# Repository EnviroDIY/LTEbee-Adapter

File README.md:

EnviroDIY LTE Bee Adapter
==============
The EnviroDIY LTE Bee Adapter shield is an interface board designed to enhance the functioning and stability of the [Digi XBee3 Cellular LTE-M/NB-IoT](https://www.digi.com/products/embedded-systems/cellular-modems/xbee3-cellular-lte-m-nb-iot) radio modules with the [EnviroDIY Mayfly Logger versions 0.5b](https://github.com/EnviroDIY/EnviroDIY_Mayfly_Logger) or earlier.

The [EnviroDIY LTE Bee Adapter shield can be purchased at Amazon.com](https://www.amazon.com/Stroud-Water-Research-Center-EnviroDIY/dp/B07TRHHMDJ).

The two main benefits of the LTE adapter board are:
- additional features for power supply, stability and switching
- status LED lights 

|  
|  
|  
|  |

The power benefits are provided via a direct JST connector to the battery, similar to Sodaq GPRSbee modules, and a capacitor chain. Power is thus much smoother, and the XBee module should not brown out and stop communicating.  Use a JST jumper wire to connect the LTEbee adapter board to the spare LIPO jack on the Mayfly board.

There are 3 colored LEDs on the LTEbee adapter.
- ON (white) light comes on anytime the LTEbee is awake.
- ASSOC (blue) light is connected to the ASSOC pin of the bee module, and will blink different patterns to show the connection status to the network.
- RSSI (orange) light is the received signal strength indicator.  It will turn on when connecting with the network vary in brightness depending on signal strength. 

DO NOT UNPLUG the LTEbee Adapter board while any of the lights are on, as this might permanently lockup your Digi radio module. Powering down the Mayfly should put set the LTEbee Adapter to put the radio into sleep mode, and this might take a minute or so after turning the Mayfly off. 

If using a Mayfly v0.5b, you'll want to make sure that the SJ13 solder jumper is in the configuration where pin 1 of the 
Mayfly bee header is powered by the 3.3Vcc and not directly to the LiPo (this is the default jumper setting).  This way, the Mayfly's bee socket only gets power whenever the Mayfly is turned on, and the LTEbee module doesn't wake up when the Mayfly is off (which is what it does if the LiPo is directly connected to bee pin 1 via SJ13).  You can then control the LTEbee module's sleep behavior with the module's pin 9 sleep pin (using Mayfly D23).

We also have access to the LTE module's reset pin now. If using the Mayfly and the ModularSensors library, the user can set the reset pin to Mayfly pin 20 in the constructor for the modem in the code sketch. Currently the only time that feature is used, though, is in transparent mode if it doesn’t reply after 4 attempts to enter command mode.  In watching the debugging logs, we haven’t seen it use that reset yet. 

The LTEbee Adapter shield also has two a solder jumper's on the back, giving the user configuration options.

The LTEbee Adapter's **SJ1 solder jumper** allows the user to select how to power the load switch for the Vcc pin of the module.  
- The default setting is that the LTE module is always powered when the Mayfly bee socket Vcc pin (pin 1) is on (as mentioned above).
- If you switch the jumper to the other position (Mayfly A5), it allows you to turn on and off the power to the LTEbee by using pin 15 of the Mayfly bee socket, which goes to the Mayfly's SJ7 solder jumper:  
  - [Mayfly SJ7](https://github.com/EnviroDIY/EnviroDIY_Mayfly_Logger#solder-jumper-connections) was originally designed to allow you to connect Mayfly pin A5 to either the RingIndicator pin (Bee 20) or the Assoc pin (Bee 15). The default is not connected to either (all pads open).
  - If you solder the Mayfly SJ7 jumper between the A5 and ASSOC pads, you are then connecting A5 to the Mayfly bee socket pin 15, which goes to SJ1 on the LTEbee_adapter, allowing you to turn on or off the LTEbee by setting A5 high or low.  We aren't sure anyone would want to do that -- since Digi recommends leaving power to the LTEbee on all the time and then command it to sleep using the sleep pin (Bee 9), rather than yanking power away from it whenever you want to turn it off -- but we added this feature to give us flexiblity in the future.

The LTEbee Adapter's **SJ2 solder jumper** is for selecting which pin on the Bee modules gets connected to Mayfly D19 (Mayfly bee header pin 12).  The default setting is for the LTEBee module's pin 13 to be connected to Mayfly D19, which is how this adapter should always be used with a Digi LTEbee, but changing SJ2 to the other setting will connect pin 12 of the bee module to D19.  This was done in case other manufacturers use the same pinout as the GPRSbee boards, which are different than the Digi LTEbee.

## License
Hardware designs shared are released, unless otherwise indicated, under the [CERN Open Hardware License 1.2](https://www.ohwr.org/projects/cernohl/wiki) (CERN_OHL).

Documentation is licensed as [Creative Commons Attribution-ShareAlike 4.0](https://creativecommons.org/licenses/by-sa/4.0/) (CC-BY-SA) copyright.

## Credits
[EnviroDIY](http://envirodiy.org/)™ is presented by the Stroud Water Research Center, with contributions from a community of enthusiasts sharing do-it-yourself ideas for environmental science and monitoring.

[Shannon Hicks](https://github.com/s-hicks2) is the primary developer of this hardware, with input from many other contributors.

This project has benefited from the support from the following funders:

* William Penn Foundation
* US Environmental Protection Agency (EPA)
* National Science Foundation, awards [EAR-0724971](http://www.nsf.gov/awardsearch/showAward?AWD_ID=0724971), [EAR-1331856](http://www.nsf.gov/awardsearch/showAward?AWD_ID=1331856), [ACI-1339834](http://www.nsf.gov/awardsearch/showAward?AWD_ID=1339834)
* Stroud Water Research Center endowment

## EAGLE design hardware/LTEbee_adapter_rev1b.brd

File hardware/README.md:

Hardware Design Files
==============

Here we provide hardware design files including [EAGLE PCB electronic design files](https://github.com/EnviroDIY/EnviroDIY_Mayfly_Logger/blob/master/hardware/Mayfly_v0p5b), for use with the EAGLE electronic design automation (EDA) software (a [free maker edition](https://www.autodesk.com/products/eagle/compare) is available).

See our Documentation pages for additional details.

For questions, use our Q&A forum at https://envirodiy.org.

## Hardware Design Credits

This hardware was developed by [Shannon Hicks](https://github.com/s-hicks2).

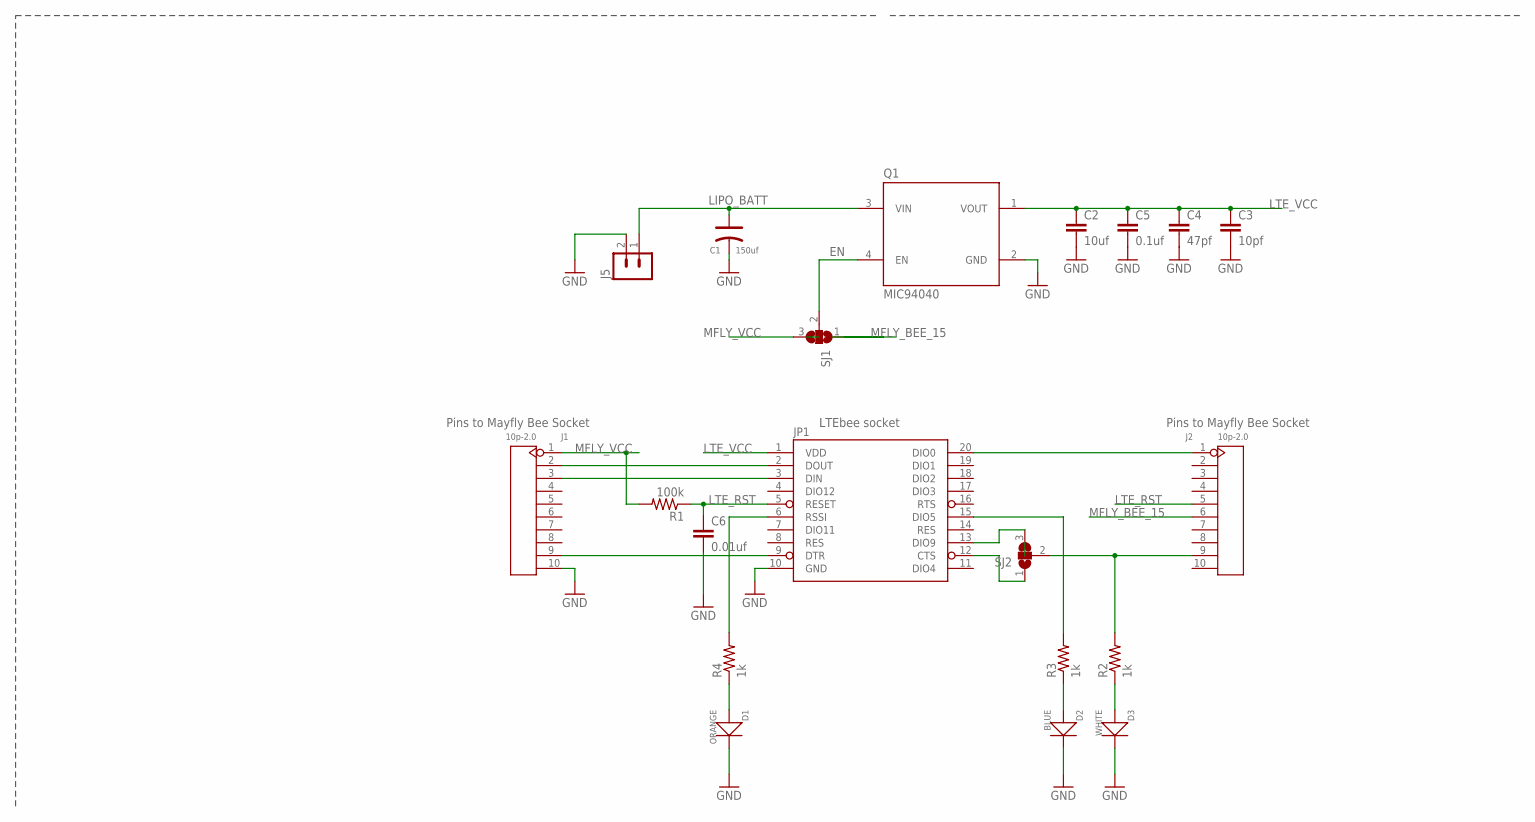
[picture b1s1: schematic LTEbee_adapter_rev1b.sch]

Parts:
C1: 150uf; AVX-B
C2: 10uf; 0402-CAP
C3: 10pf; 0402-CAP
C4: 47pf; 0402-CAP
C5: 0.1uf; 0402-CAP
C6: 0.01uf; 0402-CAP
D1: ORANGE; SOD-523
D2: BLUE; SOD-523
D3: WHITE; SOD-523
J1, J2: 10p-2.0; H10-2.0
J5: B2B-PH-K-S
JP1: XBEE-1B1; XBEE-1
Q1: MIC94040; MLF4
R1: 100k; 0603-RES
R2, R3, R4: 1k; 0603-RES
SJ1, SJ2: SJ2W; SJ_2

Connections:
EN: Q1.4 (EN), SJ1.2
GND: C1.-, C2.2, C3.2, C4.2, C5.2, C6.2, D1.-, D2.-, D3.-, J1.10, J5.2, JP1.10 (GND), Q1.2 (GND)
LIPO_BATT: C1.+, J5.1, Q1.3 (VIN)
LTE_RST: C6.1, J2.5, JP1.5 (RESET), R1.1
LTE_VCC: C2.1, C3.1, C4.1, C5.1, JP1.1 (VDD), Q1.1 (VOUT)
MFLY_BEE_15: J2.6, SJ1.1
MFLY_VCC: J1.1, R1.2, SJ1.3
unnamed: J1.2, JP1.2 (DOUT)
unnamed: J1.3, JP1.3 (DIN)
unnamed: JP1.6 (RSSI), R4.2
unnamed: D1.+, R4.1
unnamed: D3.+, R2.1
unnamed: D2.+, R3.1
unnamed: J2.9, R2.2, SJ2.2
unnamed: JP1.15 (DIO5), R3.2
unnamed: J2.1, JP1.20 (DIO0)
unnamed: J1.9, JP1.9 (DTR)
unnamed: JP1.13 (DIO9), SJ2.3
unnamed: JP1.12 (CTS), SJ2.1

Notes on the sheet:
Pins to Mayfly Bee Socket
LTEbee socket

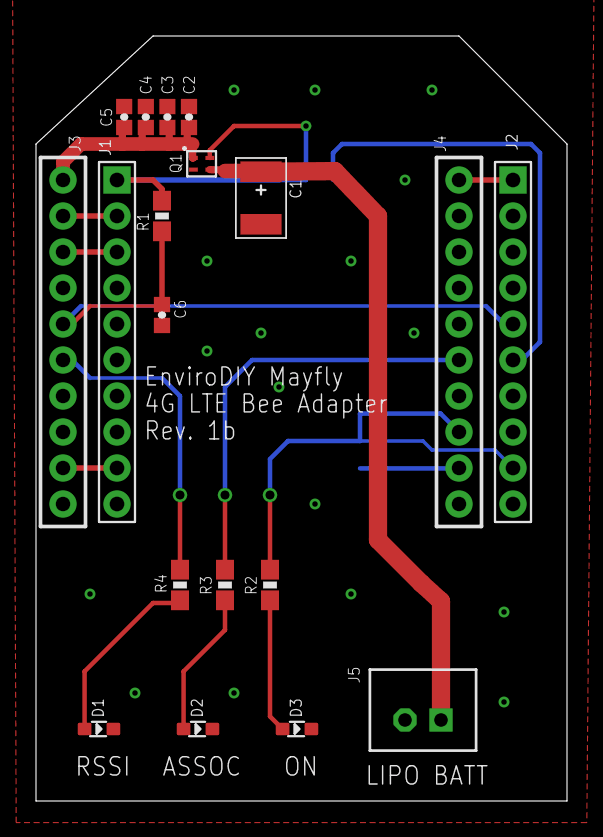
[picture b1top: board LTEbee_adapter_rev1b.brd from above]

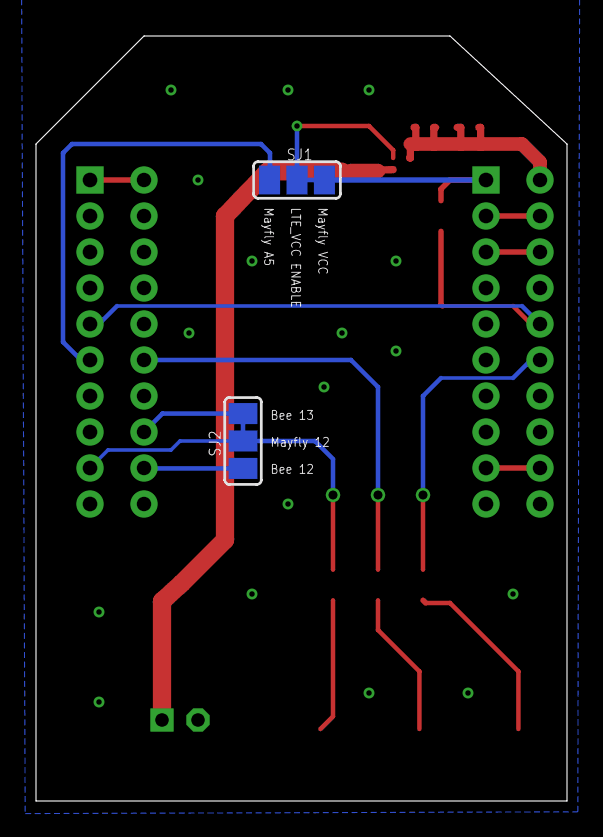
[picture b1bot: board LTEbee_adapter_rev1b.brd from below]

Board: 2 copper layers, 29.5 x 42.5 mm, 20 parts (2 on the bottom side), 19 nets.

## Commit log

2019-05-22 Add subfolders
2019-06-14 Upload pics
2019-06-14 Add pics to readme
2019-06-14 Crop & rotate LTEbee+Mayfly.jpeg
2019-08-27 Add Amazon link; unplug warning
    @s-hicks2, let me know if I got that unplug warning right.
2020-08-18 Update ReadMe to highlight lights & solder jumpers

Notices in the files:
parts and their libraries:
SparkFun-RF: Licensing: Creative Commons ShareAlike 4.0 International - https://creativecommons.org/licenses/by-sa/4.0
